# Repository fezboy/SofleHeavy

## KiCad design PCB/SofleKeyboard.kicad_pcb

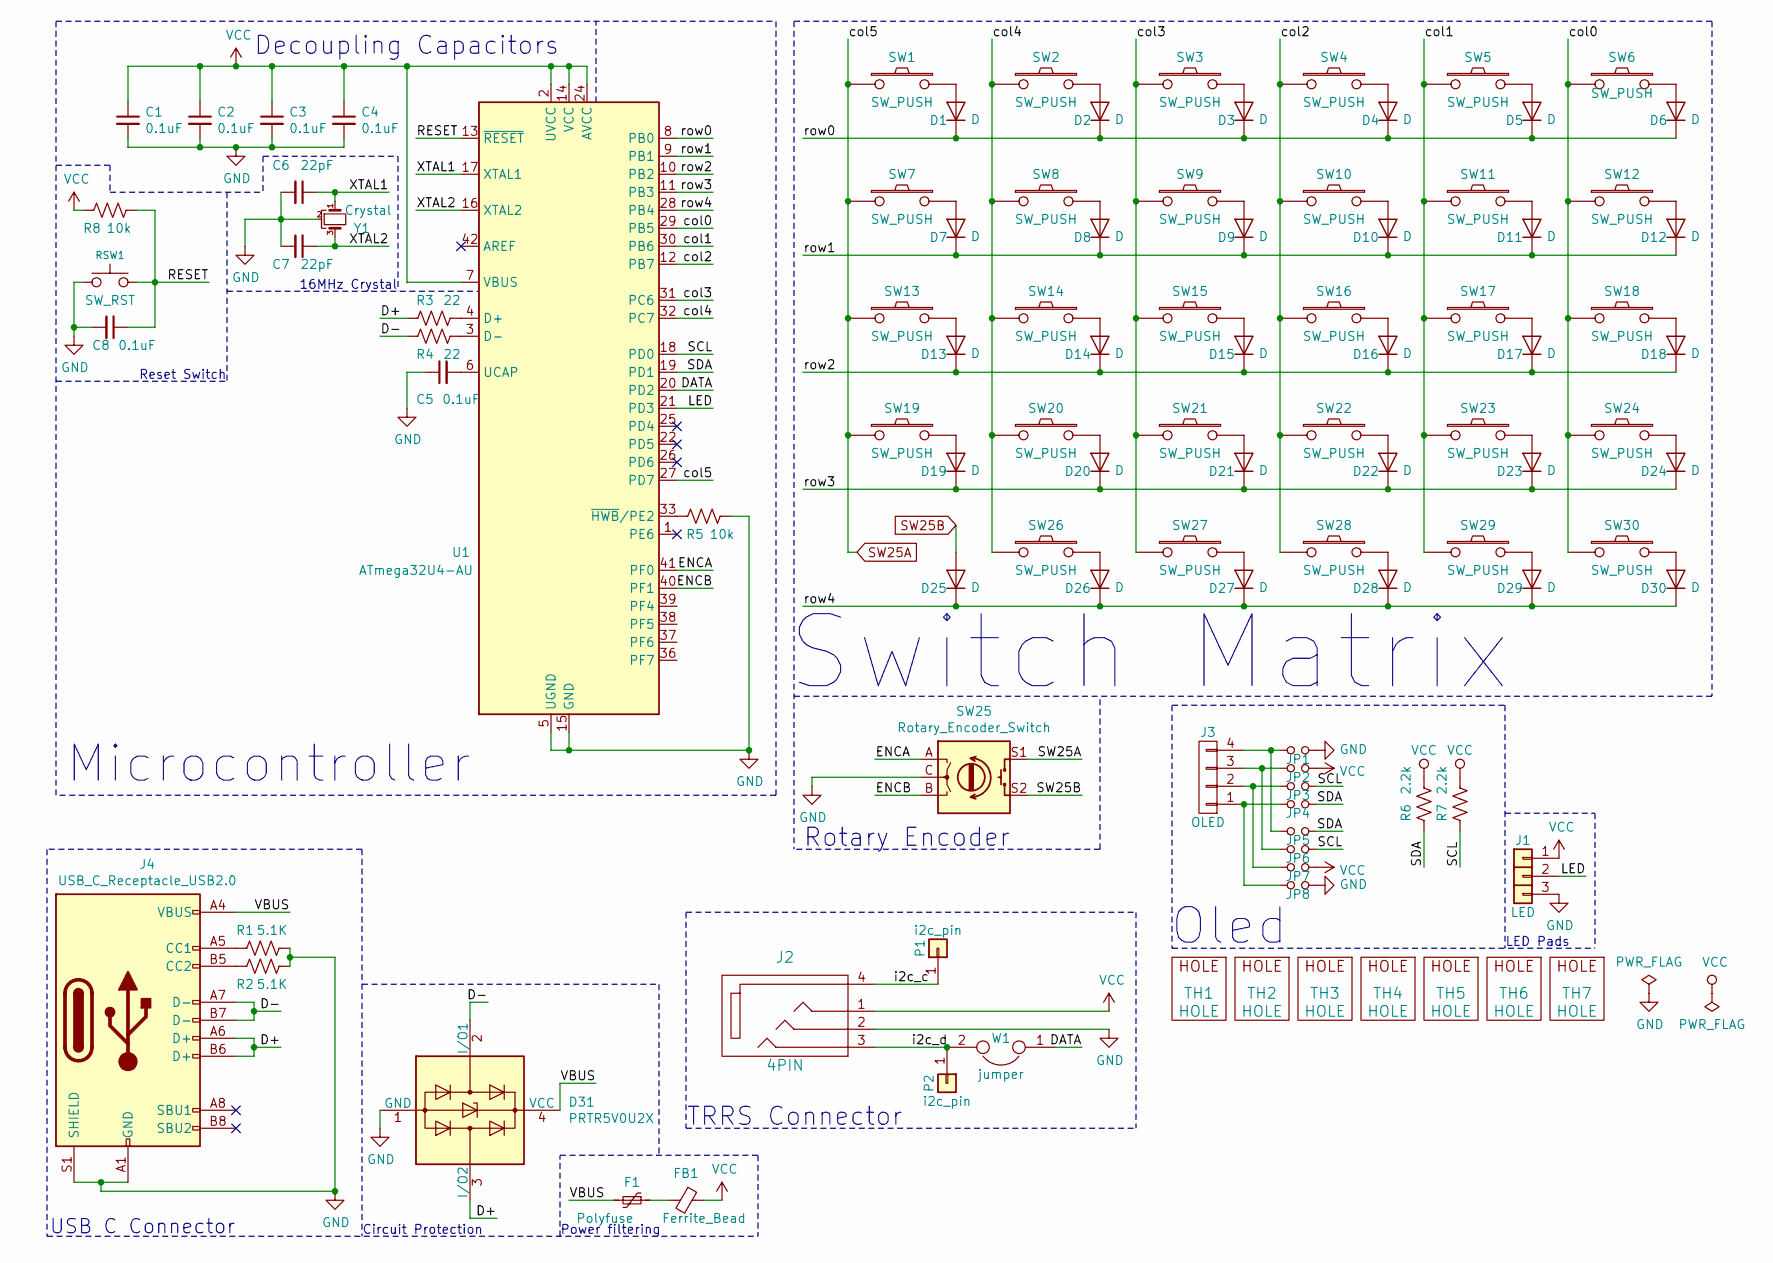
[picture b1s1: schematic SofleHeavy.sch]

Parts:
C1, C2, C3, C4, C5, C8: 0.1uF; C_0805_2012Metric_Pad1.18x1.45mm_HandSolder
C6, C7: 22pF; C_0805_2012Metric_Pad1.18x1.45mm_HandSolder
D1, D2, D3, D4, D5, D6, D7, D8, D9, D10, D11, D12, D13, D14, D15, D16, D17, D18, D19, D20, D21, D22, D23, D24, D25, D26, D27, D28, D29, D30: D; Diode_SOD123
D31: PRTR5V0U2X; SOT-143
F1: Polyfuse; Fuse_0603_1608Metric
FB1: Ferrite_Bead; L_0201_0603Metric
J1: LED
J2: 4PIN; MJ-4PP-9
J3: OLED; OLED_4Pin
J4: USB_C_Receptacle_USB2.0; USB_C_Receptacle_HRO_TYPE-C-31-M-12
JP1, JP2, JP3, JP4, JP5, JP6, JP7, JP8: Jumper_NO_Small; Jumper
P1, P2: i2c_pin; 1pin_conn
R1, R2: 5.1K; R_0201_0603Metric
R3, R4: 22; R_0201_0603Metric
R5, R8: 10k; R_0201_0603Metric
R6, R7: 2.2k; R_0201_0603Metric
RSW1: SW_RST; TACT_SWITCH_TVBP06
SW1, SW2, SW3, SW4, SW5, SW6, SW7, SW8, SW9, SW10, SW11, SW12, SW13, SW14, SW15, SW16, SW17, SW18, SW19, SW20, SW21, SW22, SW23, SW24, SW27, SW28, SW29, SW30: SW_PUSH; CherryMX_KailhLowProfile_Hotswap
SW25: Rotary_Encoder_Switch; RotaryEncoder_Alps_EC11E-Switch_Vertical_H20mm-keebio_modif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
SW26: SW_PUSH; CherryMX_KailhLowProfile_Hotswap_1.5
TH1, TH2: HOLE; M2_HOLE_PCB
TH3, TH4, TH5, TH6, TH7: HOLE; HOLE_M2_TH
U1: ATmega32U4-AU; TQFP-44_10x10mm_P0.8mm
W1: jumper; jumper_data
Y1: Crystal; Crystal_SMD_3225-4Pin_3.2x2.5mm_HandSoldering

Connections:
/D+: D31.3 (I/O2), J4.A6 (D+), J4.B6 (D+), R3.2
/D-: D31.2 (I/O1), J4.A7 (D-), J4.B7 (D-), R4.2
/DATA: U1.20 (PD2), W1.1
/ENCA: SW25.A, U1.41 (PF0)
/ENCB: SW25.B, U1.40 (PF1)
/LED: J1.2, U1.21 (PD3)
/RESET: C8.1, R8.1, RSW1.2, U1.13 (~RESET)
/SCL: JP3.2, JP6.2, R7.2, U1.18 (PD0)
/SDA: JP4.2, JP5.2, R6.2, U1.19 (PD1)
/VBUS: D31.4 (VCC), F1.2, J4.A4 (VBUS), J4.A9 (VBUS), J4.B4 (VBUS), J4.B9 (VBUS)
/XTAL1: C6.1, U1.17 (XTAL1), Y1.1
/XTAL2: C7.1, U1.16 (XTAL2), Y1.3
/col0: SW6.1, SW12.1, SW18.1, SW24.1, SW30.1, U1.29 (PB5)
/col1: SW5.1, SW11.1, SW17.1, SW23.1, SW29.1, U1.30 (PB6)
/col2: SW4.1, SW10.1, SW16.1, SW22.1, SW28.1, U1.12 (PB7)
/col3: SW3.1, SW9.1, SW15.1, SW21.1, SW27.1, U1.31 (PC6)
/col4: SW2.1, SW8.1, SW14.1, SW20.1, SW26.1, U1.32 (PC7)
/i2c_c: J2.4, P1.1
/i2c_d: J2.3, P2.1, W1.2
/row0: D1.1 (K), D2.1 (K), D3.1 (K), D4.1 (K), D5.1 (K), D6.1 (K), U1.8 (PB0)
/row1: D7.1 (K), D8.1 (K), D9.1 (K), D10.1 (K), D11.1 (K), D12.1 (K), U1.9 (PB1)
/row2: D13.1 (K), D14.1 (K), D15.1 (K), D16.1 (K), D17.1 (K), D18.1 (K), U1.10 (PB2)
/row3: D19.1 (K), D20.1 (K), D21.1 (K), D22.1 (K), D23.1 (K), D24.1 (K), U1.11 (PB3)
/row4: D25.1 (K), D26.1 (K), D27.1 (K), D28.1 (K), D29.1 (K), D30.1 (K), U1.28 (PB4)
GND: C1.2, C2.2, C3.2, C4.2, C5.1, C6.2, C7.2, C8.2, D31.1 (GND), J1.3, J2.2, J4.A1 (GND), J4.A12 (GND), J4.B1 (GND), J4.B12 (GND), J4.S1 (SHIELD), JP1.2, JP8.2, R1.1, R2.1, R5.1, RSW1.1, SW25.C, U1.5 (UGND), U1.15 (GND), U1.23 (GND), U1.35 (GND), U1.43 (GND), Y1.2
unnamed: C5.2, U1.6 (UCAP)
unnamed: D1.2 (A), SW1.2
unnamed: D2.2 (A), SW2.2
unnamed: D3.2 (A), SW3.2
unnamed: D4.2 (A), SW4.2
unnamed: D5.2 (A), SW5.2
unnamed: D6.2 (A), SW6.2
unnamed: D7.2 (A), SW7.2
unnamed: D8.2 (A), SW8.2
unnamed: D9.2 (A), SW9.2
unnamed: D10.2 (A), SW10.2
unnamed: D11.2 (A), SW11.2
unnamed: D12.2 (A), SW12.2
unnamed: D13.2 (A), SW13.2
unnamed: D14.2 (A), SW14.2
unnamed: D15.2 (A), SW15.2
unnamed: D16.2 (A), SW16.2
unnamed: D17.2 (A), SW17.2
unnamed: D18.2 (A), SW18.2
unnamed: D19.2 (A), SW19.2
unnamed: D20.2 (A), SW20.2
unnamed: D21.2 (A), SW21.2
unnamed: D22.2 (A), SW22.2
unnamed: D23.2 (A), SW23.2
unnamed: D24.2 (A), SW24.2
unnamed: D26.2 (A), SW26.2
unnamed: D27.2 (A), SW27.2
unnamed: D28.2 (A), SW28.2
unnamed: D29.2 (A), SW29.2
unnamed: D30.2 (A), SW30.2
unnamed: F1.1, FB1.2
unnamed: J3.1, JP4.1, JP8.1
unnamed: J3.2, JP3.1, JP7.1
unnamed: J3.3, JP2.1, JP6.1
unnamed: J3.4, JP1.1, JP5.1
unnamed: J4.A5 (CC1), R1.2
unnamed: J4.B5 (CC2), R2.2
unnamed: R3.1, U1.4 (D+)
unnamed: R4.1, U1.3 (D-)
unnamed: R5.2, U1.33 (~HWB~/PE2)
SW25A: SW1.1, SW7.1, SW13.1, SW19.1, SW25.S1, U1.27 (PD7)
SW25B: D25.2 (A), SW25.S2
VCC: C1.1, C2.1, C3.1, C4.1, FB1.1, J1.1, J2.1, JP2.2, JP7.2, R6.1, R7.1, R8.2, U1.2 (UVCC), U1.7 (VBUS), U1.14 (VCC), U1.24 (AVCC), U1.34 (VCC), U1.44 (AVCC); also elsewhere on the board

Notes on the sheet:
Oled
Decoupling Capacitors
Reset Switch
16MHz Crystal
Microcontroller
Circuit Protection
Power filtering
USB C Connector
Rotary Encoder
TRRS Connector
LED Pads
Switch Matrix

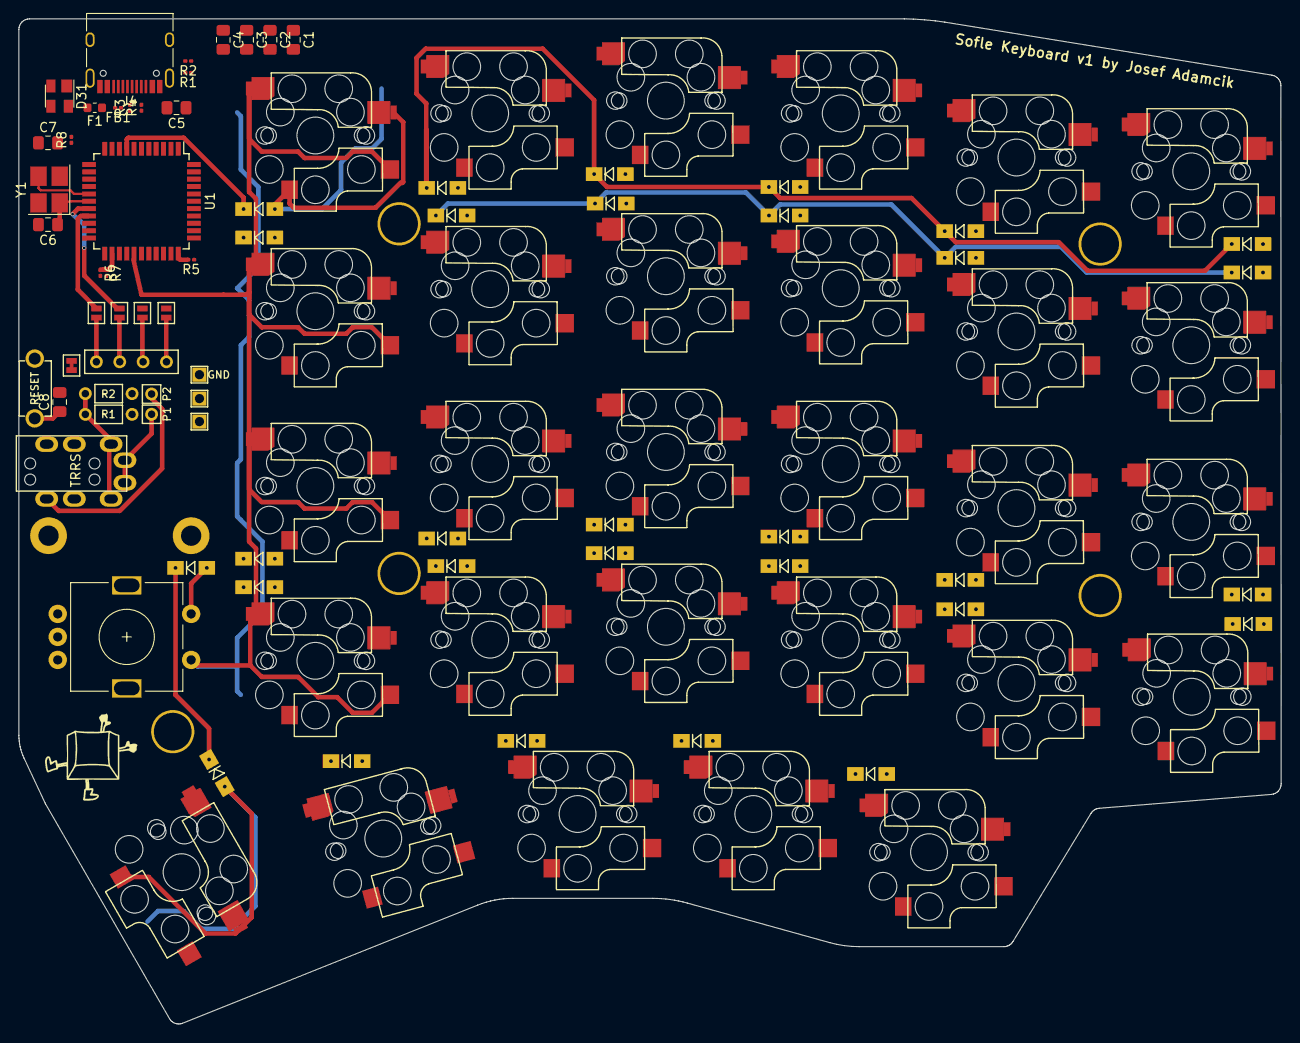
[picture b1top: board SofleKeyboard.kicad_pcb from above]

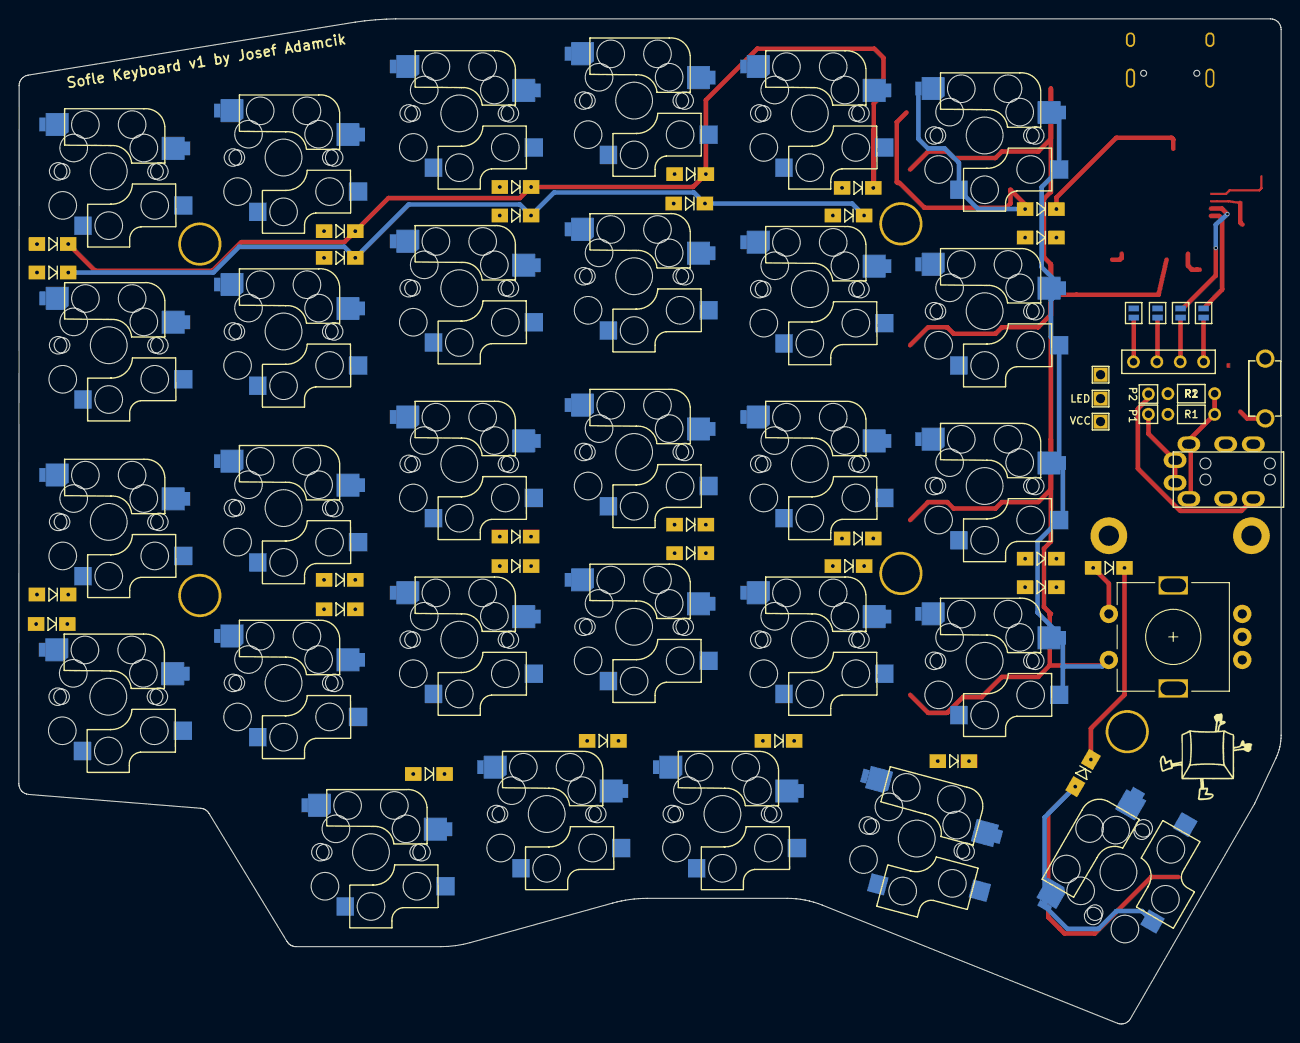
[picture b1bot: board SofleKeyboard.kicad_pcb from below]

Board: 2 copper layers, 137.2 x 109.2 mm, 108 parts (5 on the bottom side), 68 nets.

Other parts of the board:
R1#2, R2#2: R; RESISTOR_mini
Ref**: Val**; SofleLogoSmall
Ref**#2: Val**; SofleLogoSmall

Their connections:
VCC: R1#2.1, R2#2.1; also elsewhere on the board

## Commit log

2020-11-28 add autosave to .gitignore
2020-11-28 replace pro-micro with ATmega32u4-AU
2020-11-28 Started PCB redux
